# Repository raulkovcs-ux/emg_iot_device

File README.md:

# FAMA-Band: an 8-channel sEMG armband for FAMA-Net

An end-user research device for the **FAMA-Net** thesis (fatigue-aware,
multi-scale adaptive CNN for sEMG gesture recognition). It records
forearm EMG at an exactly known 1 kHz, logs it losslessly, streams it to
the lab PC, and runs FAMA-Net, including both online adaptation tiers,
**on the device**.

| | |
|---|---|
| Channels | 8 bipolar, active dry electrodes (10 mm ENIG, 20 mm IED), driven right leg |
| Sampling | ADS1298 24-bit at 2000 SPS → **1000.00 Hz ± 20 ppm** output, flat ±0.06 dB over 20–450 Hz |
| Noise | 1.61 µVrms input-referred (20–450 Hz, calculated), 105 dB dynamic range |
| Processing | ESP32-S3: thesis pre-processing, STFT [8 × 33 × 9], FAMA-Net, Tier A (causal AdaBN), Tier B (SampEn-triggered head fine-tuning) |
| Data | microSD raw log (2 kSPS) + Wi-Fi UDP or BLE 5 stream, protocol markers in the device timebase |
| Power | 600 mAh Li-Po, ≈5.4 h (BLE) / ≈3.6 h (Wi-Fi) estimated; battery-only while worn with a hardware USB interlock |
| Size | Hub 76 × 50 × 20 mm, pods 19 × 37 × 10.5 mm |
| Prosthesis variant | Electrodes in a transradial socket, **rigid-flex hub** wrapped around the socket, prosthetic-hand interface (UART + 2 proportional outputs) |

## What's in the repository

| Folder | Content | Status |
|---|---|---|
| [`docs/`](docs) | Research, specification, hardware, mechanics, firmware, safety and ethics, bring-up, wearing protocol, thesis mapping | complete |
| [`hardware/`](hardware) | KiCad 7 projects (hub: 4 layers, socket hub: 4-layer rigid-flex, pod: 2 layers), schematic PDFs, Gerbers, BOM and pick-and-place, STEP; Python generators | ERC clean, DRC: 0 errors, 0 unconnected |
| [`mechanical/`](mechanical) | Parametric OpenSCAD: armband enclosures (`famaband.scad`) and transradial socket, electrode cartridges, hub carrier, forearm frame (`socket.scad`); STLs, renders | armband ready to print; socket needs a check-socket fitting |
| [`firmware/`](firmware) | ESP-IDF v5.3 application + portable DSP/ML core (`components/fama_dsp`) | builds (Wi-Fi, BLE and socket/hand-interface variants) |
| [`host/`](host) | Python package `famaband`: reference DSP/model, PyTorch FAMA-Net + exporter, recorder, protocol runner, contact check, simulator; tests | 35 tests passing |

## Documentation

1. [Research: why a custom device, design decisions](docs/01_research.md)
2. [Specification: numbered requirements traced to the thesis](docs/02_specification.md)
3. [Hardware design: circuits, noise, power, safety numbers, PCB](docs/03_hardware_design.md)
4. [Mechanical design](docs/04_mechanical.md)
5. [Firmware and host software](docs/05_firmware.md)
6. [Safety and ethics for use on people](docs/06_safety_and_ethics.md) (**read before any human use**)
7. [Ordering, assembly, bring-up and safety tests](docs/07_assembly_and_bringup.md)
8. [Wearing the band and running a session](docs/08_wearing_and_session_protocol.md)
9. [How the device closes open items of the thesis review sheet](docs/09_thesis_integration.md)
10. [**Prosthetic socket integration and rigid-flex hub**](docs/10_prosthetic_socket.md)

| Socket variant | Rigid-flex socket hub |
|---|---|
|  |  |

| Hub PCB (top) | Pod (top and skin side) |
|---|---|
|  |  |

## Quick start

```bash
make test        # build the C core for the host and run all tests (needs numpy, scipy, pytest; torch optional)
make hardware    # regenerate schematics + PCBs + fab outputs (KiCad 7, Java, xvfb; about 15 min)
make firmware    # ESP-IDF v5.3 build for the ESP32-S3
make stl         # export enclosure STLs (OpenSCAD)

# with a device (or the simulator: python -m famaband.simulator_device)
cd host
python -m famaband.contact                         # electrode contact check
python -m famaband.protocol_runner --subject S01 --day 1
python -m famaband.io recordings/S01_D1_*.fbr --npz s01d1.npz
```

## Verification status, stated honestly

* **Verified in this repository:**
  * the schematics match the source netlist (KiCad's own netlister) and pass ERC
  * both PCBs pass DRC with no unconnected pads
  * the firmware compiles for the ESP32-S3
  * the firmware's signal chain, network runtime, Tier A/B logic and packet format are tested against independent Python references
  * the protocol tools are tested end to end over UDP against a software device
  * the ADS1298 pinout was cross-checked: the stock KiCad 7.0 symbol swaps pins 3/4, and a corrected symbol is used
* **Not yet verified (needs the physical boards):** analog noise and
  CMRR, sample-rate accuracy, battery life, on-device inference timing,
  radio robustness, fault currents and interlock timing. The procedures
  and pass criteria are in [`docs/07_assembly_and_bringup.md`](docs/07_assembly_and_bringup.md).
  Figures marked "estimate" in the docs come from datasheets and
  calculation.
* **Not a medical device.** Research prototype; ethics approval and
  informed consent are required before any recording on people.

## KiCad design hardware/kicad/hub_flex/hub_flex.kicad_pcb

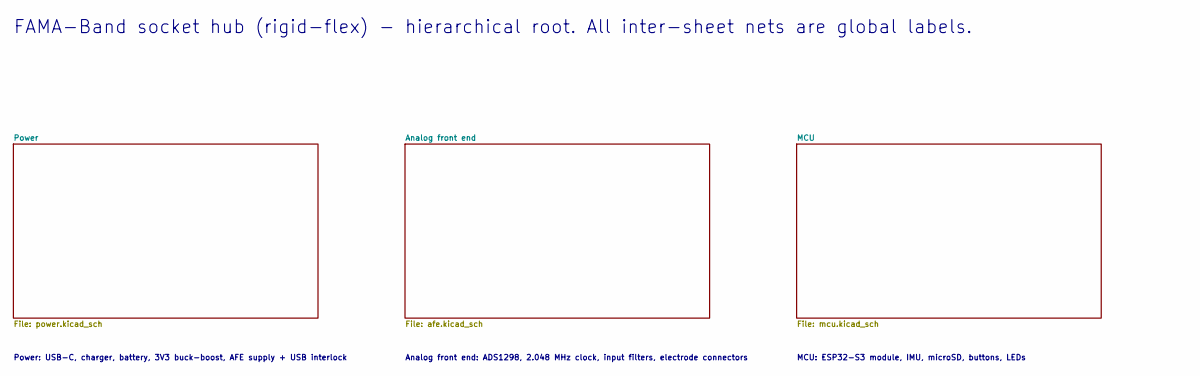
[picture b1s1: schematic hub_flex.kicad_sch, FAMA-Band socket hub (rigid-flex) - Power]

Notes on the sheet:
Power: USB-C, charger, battery, 3V3 buck-boost, AFE supply + USB interlock
Analog front end: ADS1298, 2.048 MHz clock, input filters, electrode connectors
MCU: ESP32-S3 module, IMU, microSD, buttons, LEDs
FAMA-Band socket hub (rigid-flex) - hierarchical root. All inter-sheet nets are global labels.

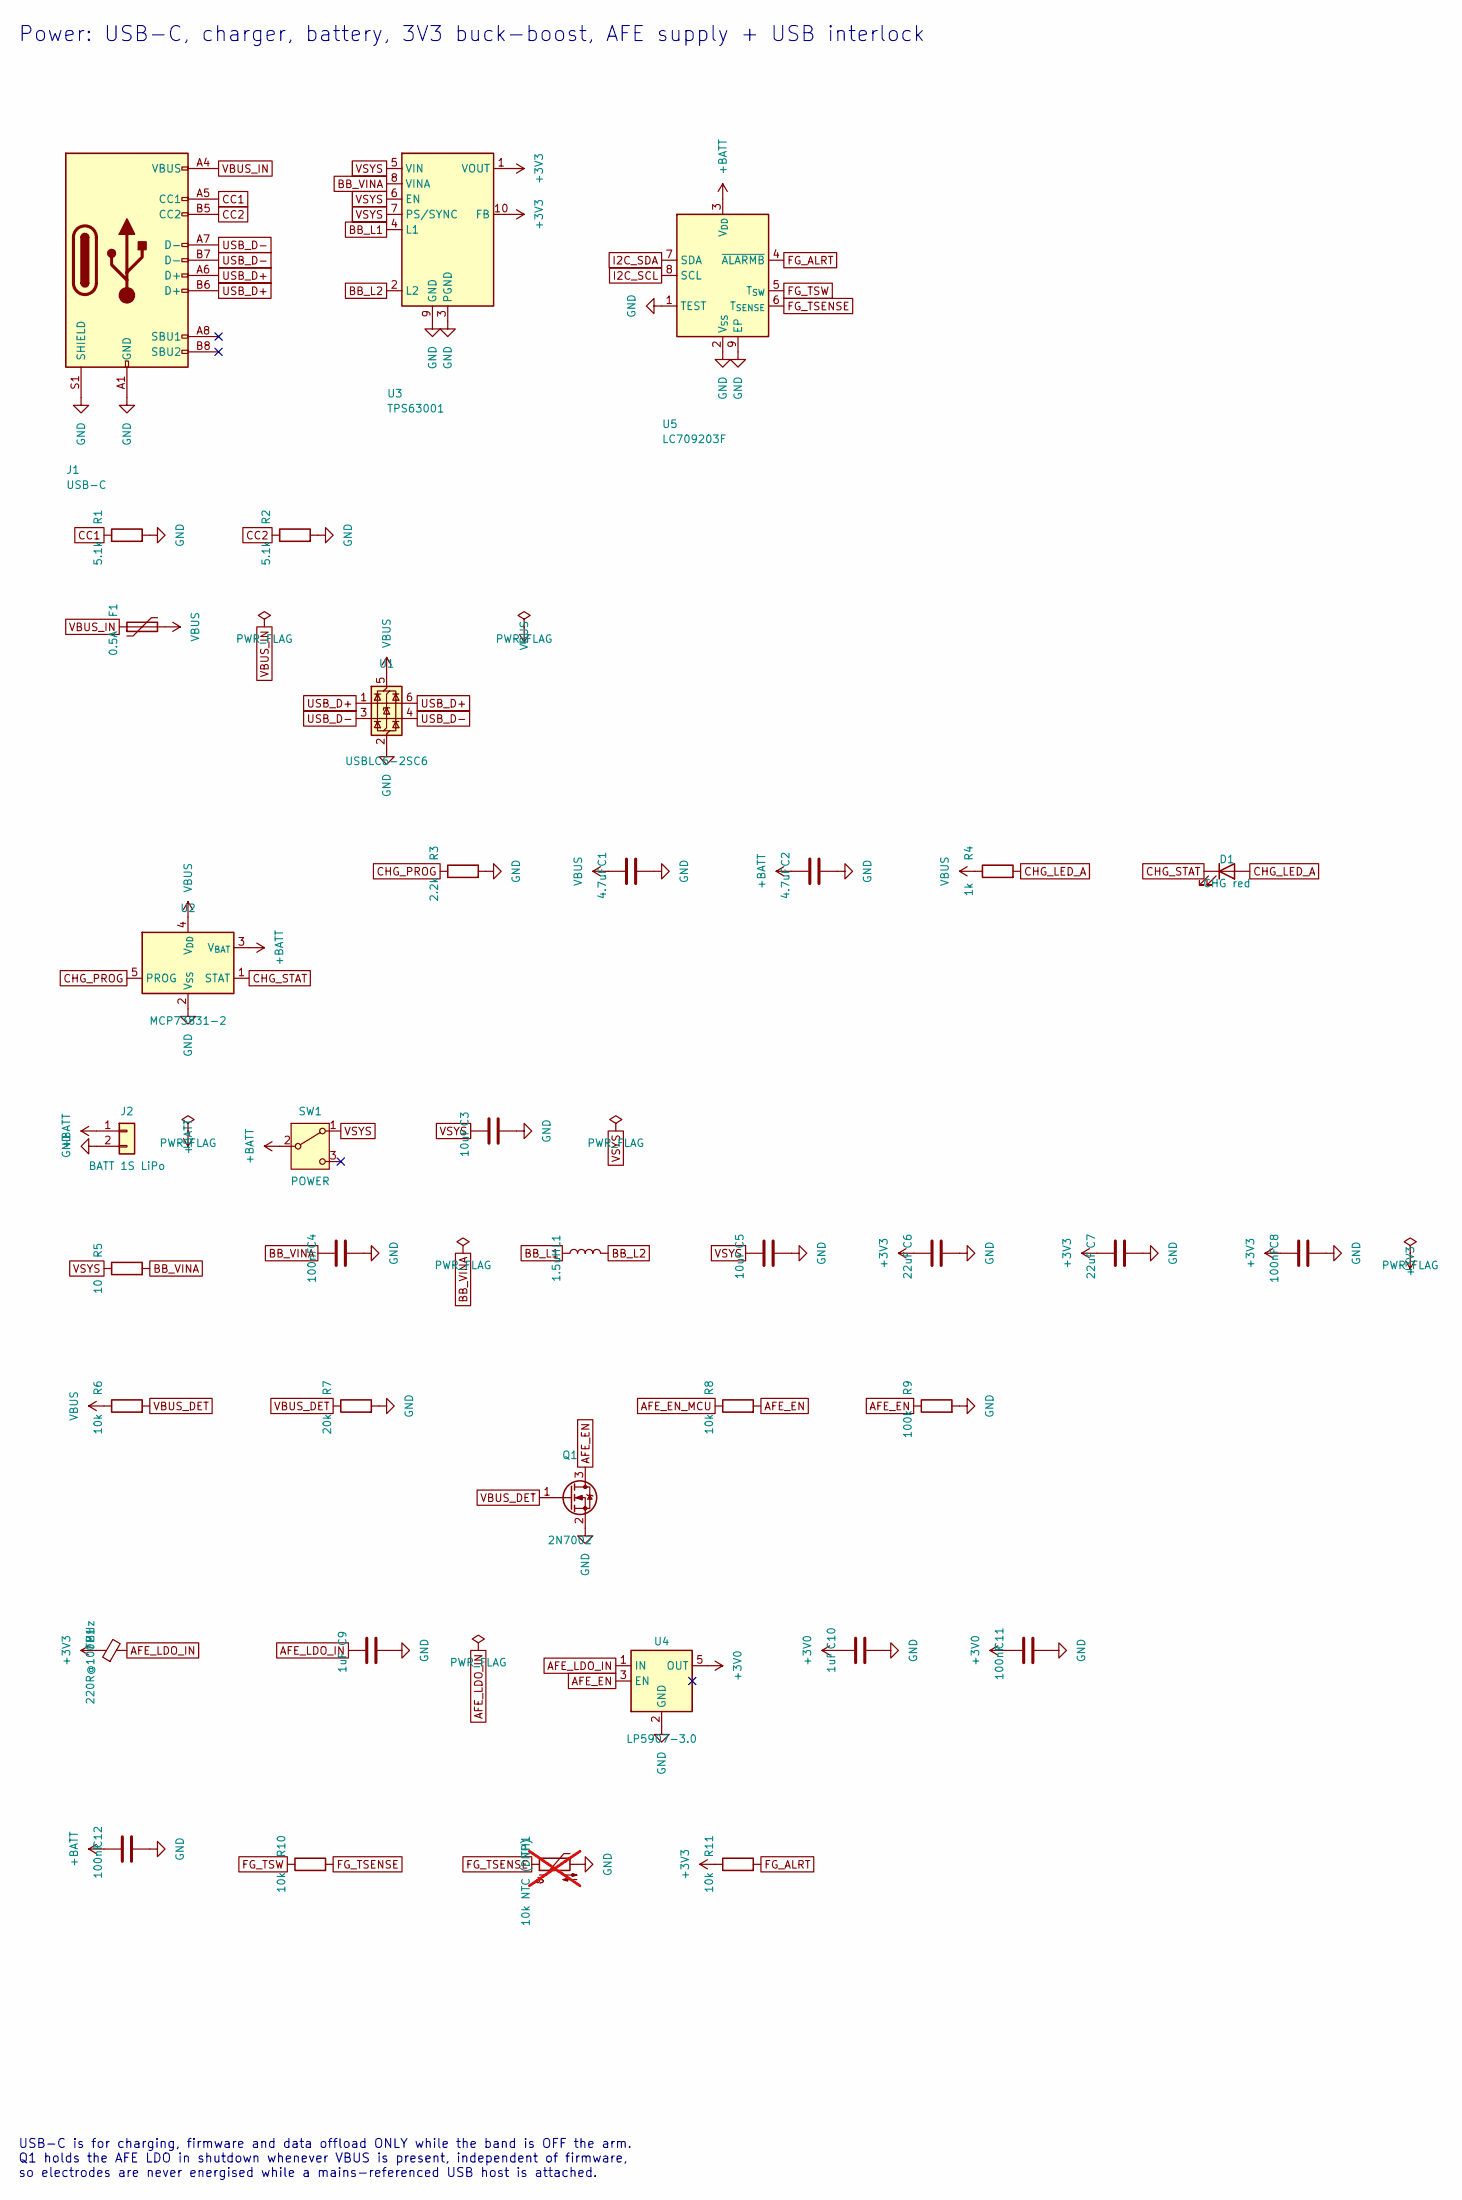
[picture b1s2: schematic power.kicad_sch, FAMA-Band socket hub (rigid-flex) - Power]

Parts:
C1, C2: 4.7uF; C_0603_1608Metric
C3, C5: 10uF; C_0805_2012Metric
C4, C8, C11, C12: 100nF; C_0402_1005Metric
C6, C7: 22uF; C_0805_2012Metric
C9, C10: 1uF; C_0402_1005Metric
D1: CHG red; LED_0603_1608Metric; MPN 150060RS75000
F1: 0.5A; Fuse_0805_2012Metric
FB1: 220R@100MHz; L_0603_1608Metric; MPN BLM18PG221SN1D
J1: USB-C; USB_C_Receptacle_HRO_TYPE-C-31-M-12; MPN TYPE-C-31-M-12
J2: BATT 1S LiPo; JST_PH_S2B-PH-SM4-TB_1x02-1MP_P2.00mm_Horizontal; MPN S2B-PH-SM4-TB(LF)(SN)
L1: 1.5uH; L_Coilcraft_XxL4020; MPN XFL4020-152MEC
Q1: 2N7002; SOT-23; MPN 2N7002
R1, R2: 5.1k; R_0402_1005Metric
R3: 2.2k; R_0402_1005Metric
R4: 1k; R_0402_1005Metric
R5: 10; R_0402_1005Metric
R6, R8, R10, R11: 10k; R_0402_1005Metric
R7: 20k; R_0402_1005Metric
R9: 100k; R_0402_1005Metric
SW1: POWER; SW_SPDT_PCM12; MPN PCM12SMTR
TH1: 10k NTC (DNP); R_0402_1005Metric; MPN NCP15XH103F03RC; not fitted
U1: USBLC6-2SC6; SOT-23-6; MPN USBLC6-2SC6
U2: MCP73831-2; SOT-23-5; MPN MCP73831T-2ACI/OT
U3: TPS63001; Texas_DRC0010J_ThermalVias; MPN TPS63001DRCR
U4: LP5907-3.0; SOT-23-5; MPN LP5907MFX-3.0/NOPB
U5: LC709203F; WDFN-8-1EP_4x3mm_P0.65mm_EP2.4x1.8mm; MPN LC709203FQH-01TWG

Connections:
+3V0: C10.1, C11.1, U4.5 (OUT); also elsewhere on the board
+3V3: C6.1, C7.1, C8.1, FB1.1, R11.1, U3.1 (VOUT), U3.10 (FB); also elsewhere on the board
+BATT: C2.1, C12.1, J2.1, SW1.2 (B), U2.3 (V_{BAT}), U5.3 (V_{DD})
AFE_EN: Q1.3 (D), R8.2, R9.1, U4.3 (EN)
AFE_EN_MCU: R8.1; also elsewhere on the board
AFE_LDO_IN: C9.1, FB1.2, U4.1 (IN)
BB_L1: L1.1, U3.4 (L1)
BB_L2: L1.2, U3.2 (L2)
BB_VINA: C4.1, R5.2, U3.8 (VINA)
CC1: J1.A5 (CC1), R1.1
CC2: J1.B5 (CC2), R2.1
CHG_LED_A: D1.2 (A), R4.2
CHG_PROG: R3.1, U2.5 (PROG)
CHG_STAT: D1.1 (K), U2.1 (STAT)
FG_ALRT: R11.2, U5.4 (~ALARMB); also elsewhere on the board
FG_TSENSE: R10.2, TH1.1, U5.6 (T_{SENSE})
FG_TSW: R10.1, U5.5 (T_{SW})
GND: C1.2, C2.2, C3.2, C4.2, C5.2, C6.2, C7.2, C8.2, C9.2, C10.2, C11.2, C12.2, J1.A1 (GND), J1.A12 (GND), J1.B1 (GND), J1.B12 (GND), J1.S1 (SHIELD), J2.2, Q1.2 (S), R1.2, R2.2, R3.2, R7.2, R9.2, TH1.2, U1.2 (GND), U2.2 (V_{SS}), U3.3 (PGND), U3.9 (GND), U3.11 (PGND), U4.2 (GND), U5.1 (TEST), U5.2 (V_{SS}), U5.9 (EP); also elsewhere on the board
I2C_SCL: U5.8 (SCL); also elsewhere on the board
I2C_SDA: U5.7 (SDA); also elsewhere on the board
USB_D+: J1.A6 (D+), J1.B6 (D+), U1.1 (I/O1), U1.6 (I/O1); also elsewhere on the board
USB_D-: J1.A7 (D-), J1.B7 (D-), U1.3 (I/O2), U1.4 (I/O2); also elsewhere on the board
VBUS: C1.1, F1.2, R4.1, R6.1, U1.5 (VBUS), U2.4 (V_{DD})
VBUS_DET: Q1.1 (G), R6.2, R7.1; also elsewhere on the board
VBUS_IN: F1.1, J1.A4 (VBUS), J1.A9 (VBUS), J1.B4 (VBUS), J1.B9 (VBUS)
VSYS: C3.1, C5.1, R5.1, SW1.1 (A), U3.5 (VIN), U3.6 (EN), U3.7 (PS/SYNC)

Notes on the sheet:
Power: USB-C, charger, battery, 3V3 buck-boost, AFE supply + USB interlock
USB-C is for charging, firmware and data offload ONLY while the band is OFF the arm. Q1 holds the AFE LDO in shutdown whenever VBUS is present, independent of firmware, so electrodes are never energised while a mains-referenced USB host is attached.

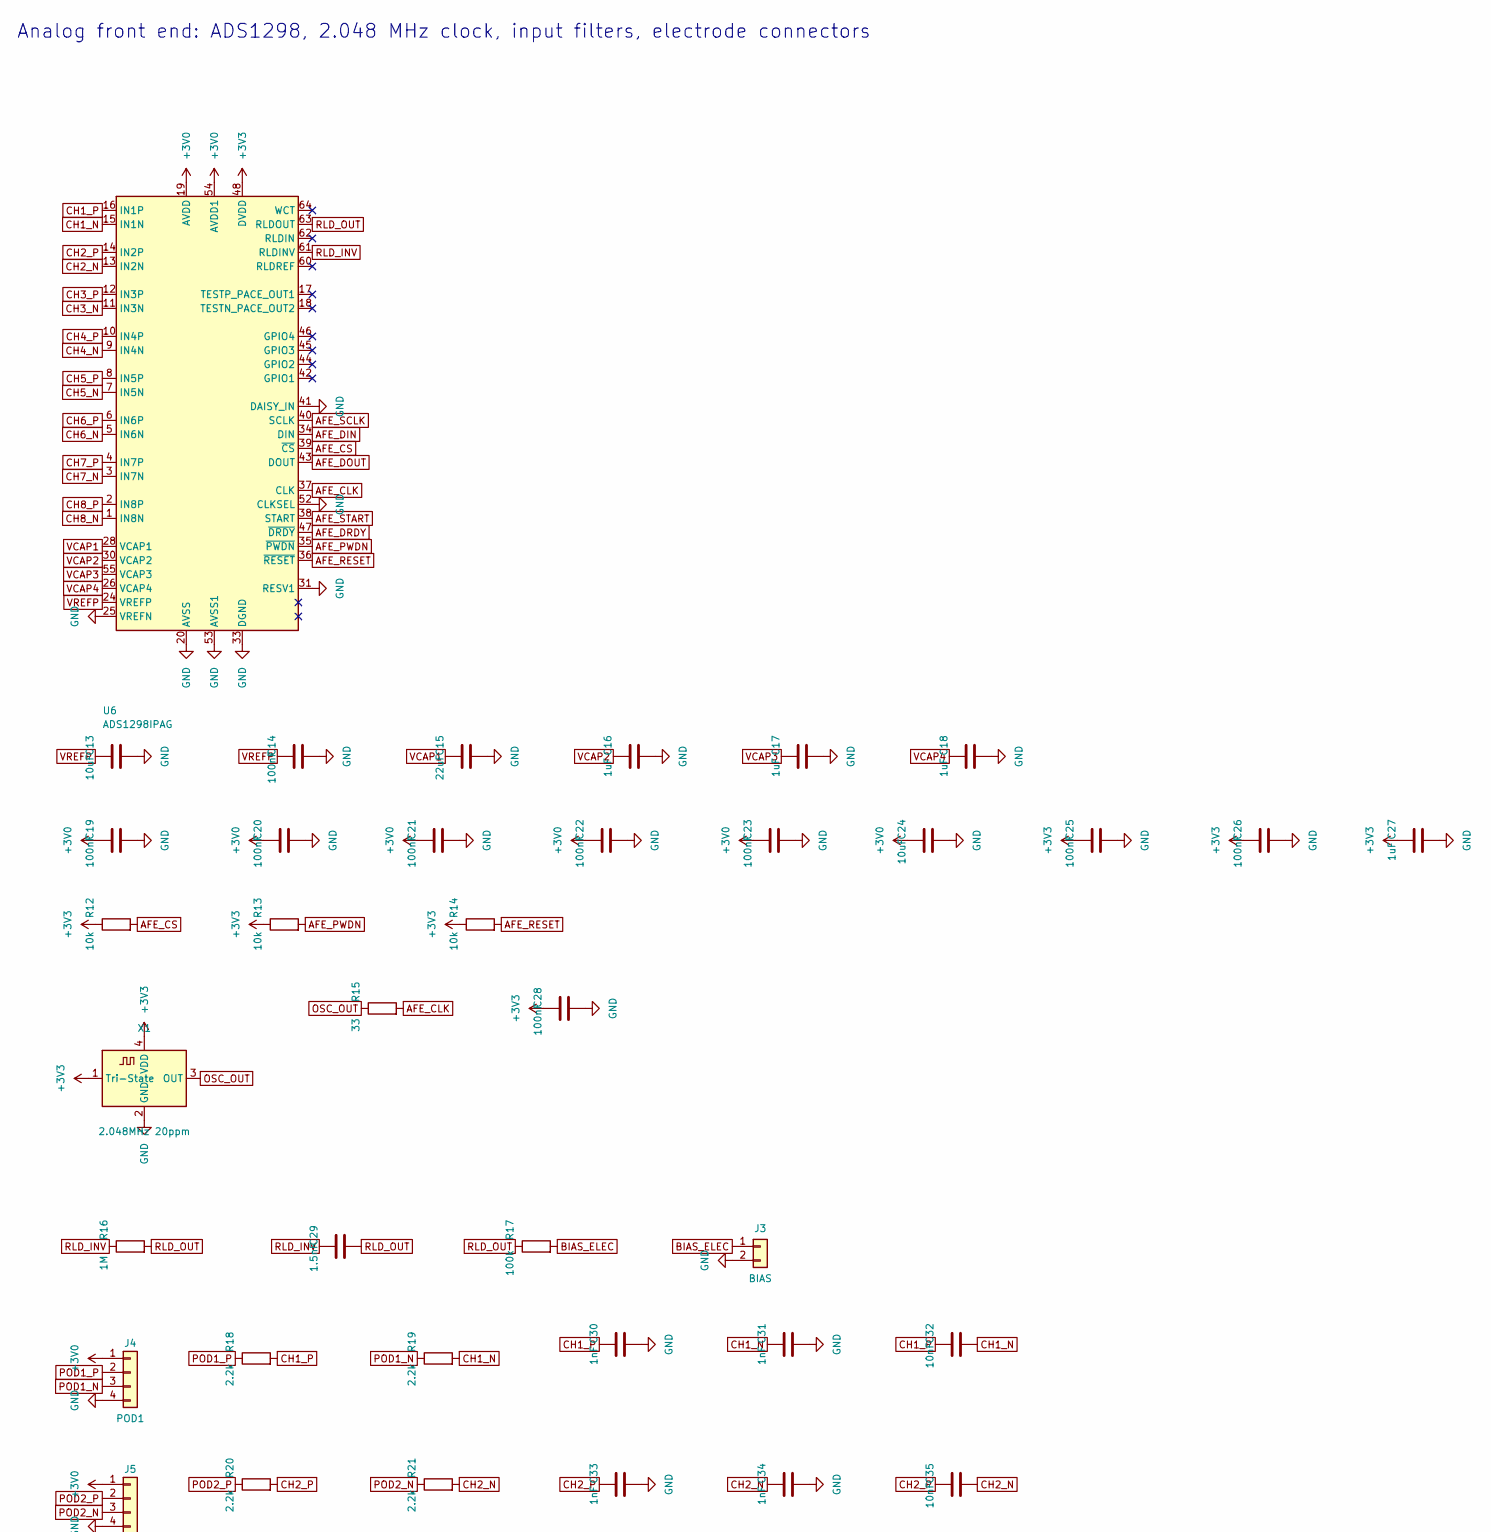
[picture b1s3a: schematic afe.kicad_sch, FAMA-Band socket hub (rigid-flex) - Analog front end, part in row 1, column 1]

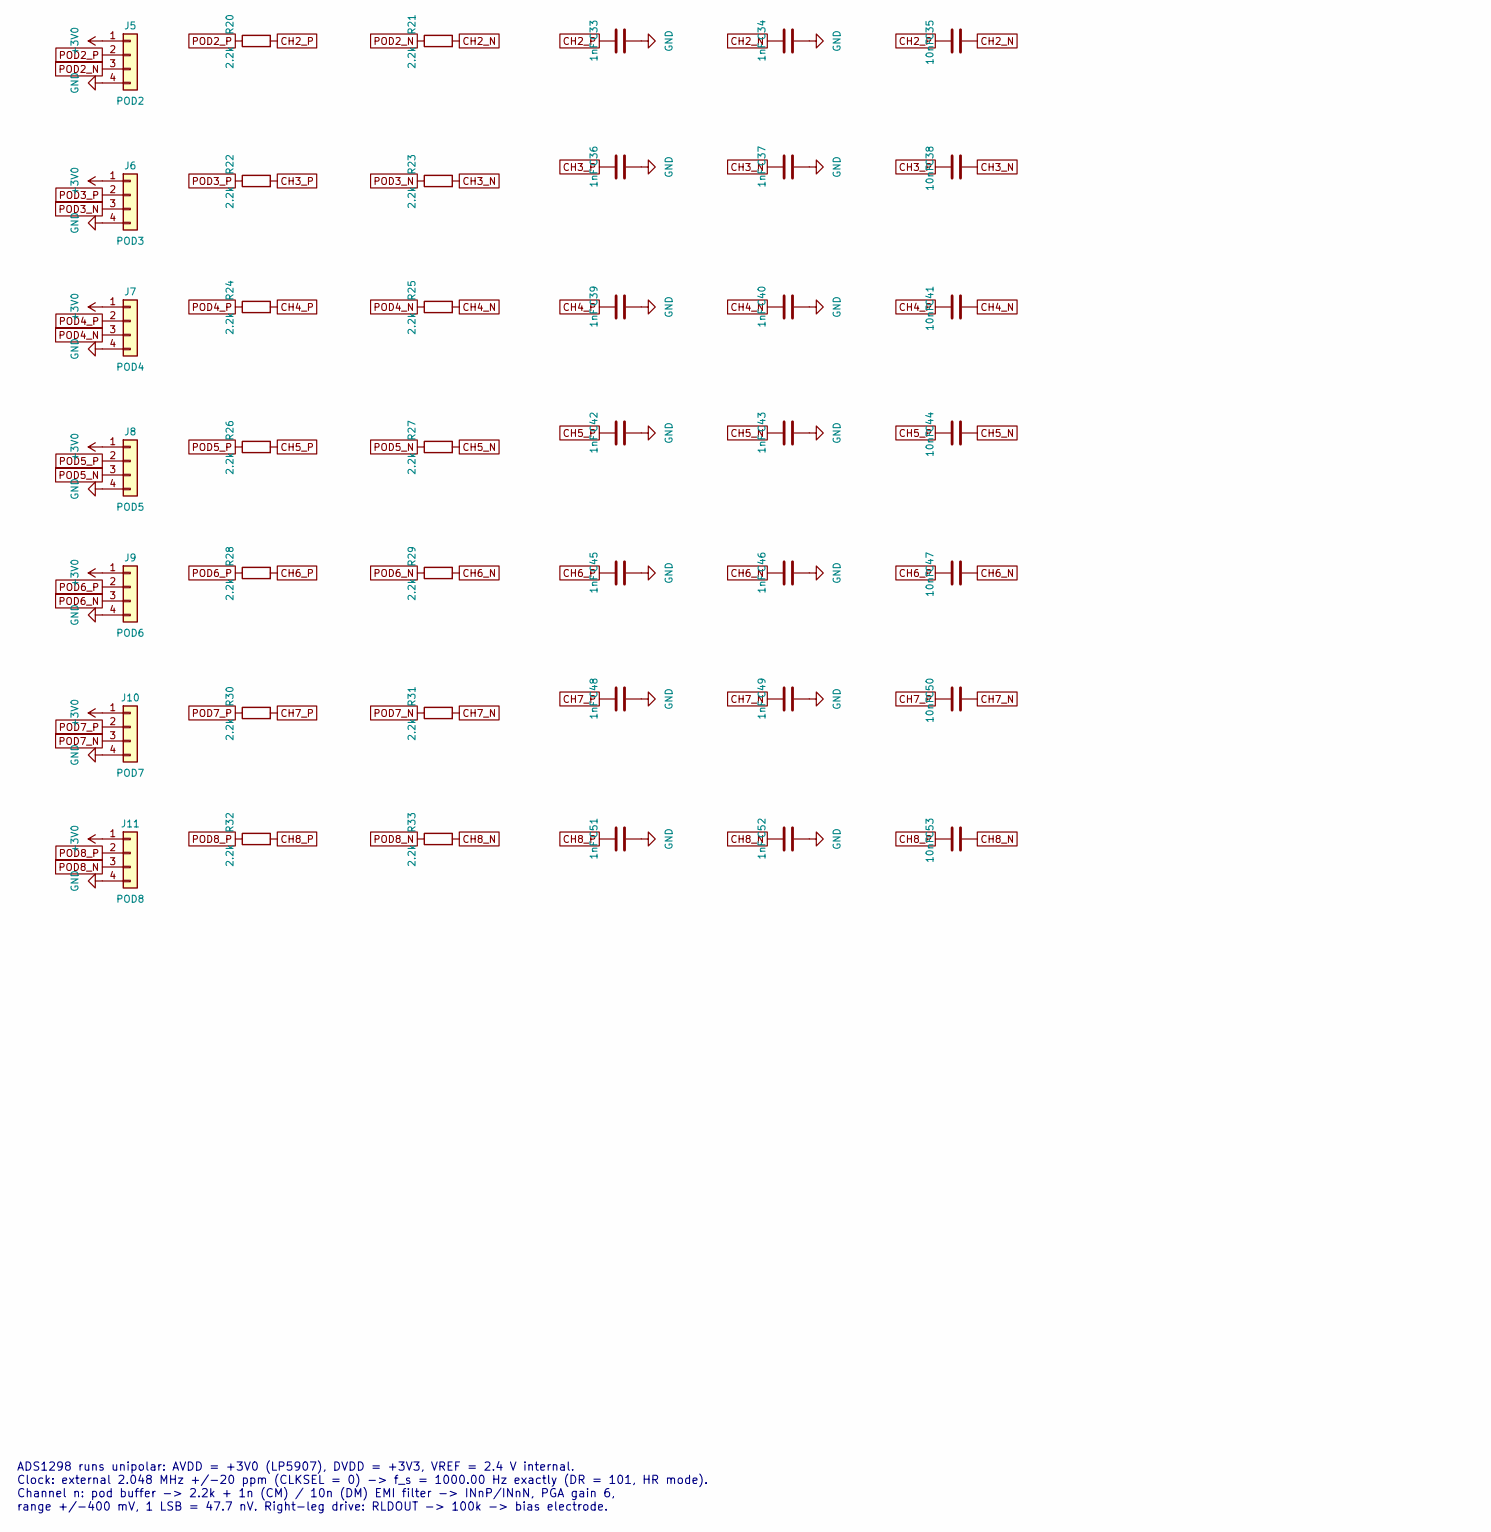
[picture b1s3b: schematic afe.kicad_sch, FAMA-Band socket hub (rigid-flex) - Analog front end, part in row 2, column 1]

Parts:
C13, C24: 10uF; C_0603_1608Metric
C14, C19, C20, C21, C22, C23, C25, C26, C28: 100nF; C_0402_1005Metric
C15: 22uF; C_0805_2012Metric
C16, C17, C18, C27: 1uF; C_0402_1005Metric
C29: 1.5nF; C_0402_1005Metric
C30, C31, C33, C34, C36, C37, C39, C40, C42, C43, C45, C46, C48, C49, C51, C52: 1nF; C_0402_1005Metric
C32, C35, C38, C41, C44, C47, C50, C53: 10nF; C_0402_1005Metric
J3: BIAS; JST_GH_SM02B-GHS-TB_1x02-1MP_P1.25mm_Horizontal; MPN SM02B-GHS-TB(LF)(SN)
J4: POD1; JST_GH_SM04B-GHS-TB_1x04-1MP_P1.25mm_Horizontal; MPN SM04B-GHS-TB(LF)(SN)
J5: POD2; JST_GH_SM04B-GHS-TB_1x04-1MP_P1.25mm_Horizontal; MPN SM04B-GHS-TB(LF)(SN)
J6: POD3; JST_GH_SM04B-GHS-TB_1x04-1MP_P1.25mm_Horizontal; MPN SM04B-GHS-TB(LF)(SN)
J7: POD4; JST_GH_SM04B-GHS-TB_1x04-1MP_P1.25mm_Horizontal; MPN SM04B-GHS-TB(LF)(SN)
J8: POD5; JST_GH_SM04B-GHS-TB_1x04-1MP_P1.25mm_Horizontal; MPN SM04B-GHS-TB(LF)(SN)
J9: POD6; JST_GH_SM04B-GHS-TB_1x04-1MP_P1.25mm_Horizontal; MPN SM04B-GHS-TB(LF)(SN)
J10: POD7; JST_GH_SM04B-GHS-TB_1x04-1MP_P1.25mm_Horizontal; MPN SM04B-GHS-TB(LF)(SN)
J11: POD8; JST_GH_SM04B-GHS-TB_1x04-1MP_P1.25mm_Horizontal; MPN SM04B-GHS-TB(LF)(SN)
R12, R13, R14: 10k; R_0402_1005Metric
R15: 33; R_0402_1005Metric
R16: 1M; R_0402_1005Metric
R17: 100k; R_0603_1608Metric
R18, R19, R20, R21, R22, R23, R24, R25, R26, R27, R28, R29, R30, R31, R32, R33: 2.2k; R_0402_1005Metric
U6: ADS1298IPAG; TQFP-64_10x10mm_P0.5mm; MPN ADS1298IPAG
X1: 2.048MHz 20ppm; Oscillator_SMD_ECS_2520MV-xxx-xx-4Pin_2.5x2.0mm; MPN SiT8008BI-xx-33E-2.048000

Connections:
+3V0: C19.1, C20.1, C21.1, C22.1, C23.1, C24.1, J4.1, J5.1, J6.1, J7.1, J8.1, J9.1, J10.1, J11.1, U6.19 (AVDD), U6.21 (AVDD), U6.22 (AVDD), U6.54 (AVDD1), U6.56 (AVDD), U6.59 (AVDD); also elsewhere on the board
+3V3: C25.1, C26.1, C27.1, C28.1, R12.1, R13.1, R14.1, U6.48 (DVDD), U6.50 (DVDD), X1.1 (Tri-State), X1.4 (VDD); also elsewhere on the board
AFE_CLK: R15.2, U6.37 (CLK)
AFE_CS: R12.2, U6.39 (~CS); also elsewhere on the board
AFE_DIN: U6.34 (DIN); also elsewhere on the board
AFE_DOUT: U6.43 (DOUT); also elsewhere on the board
AFE_DRDY: U6.47 (~DRDY); also elsewhere on the board
AFE_PWDN: R13.2, U6.35 (~PWDN); also elsewhere on the board
AFE_RESET: R14.2, U6.36 (~RESET); also elsewhere on the board
AFE_SCLK: U6.40 (SCLK); also elsewhere on the board
AFE_START: U6.38 (START); also elsewhere on the board
BIAS_ELEC: J3.1, R17.2
CH1_N: C31.1, C32.2, R19.2, U6.15 (IN1N)
CH1_P: C30.1, C32.1, R18.2, U6.16 (IN1P)
CH2_N: C34.1, C35.2, R21.2, U6.13 (IN2N)
CH2_P: C33.1, C35.1, R20.2, U6.14 (IN2P)
CH3_N: C37.1, C38.2, R23.2, U6.11 (IN3N)
CH3_P: C36.1, C38.1, R22.2, U6.12 (IN3P)
CH4_N: C40.1, C41.2, R25.2, U6.9 (IN4N)
CH4_P: C39.1, C41.1, R24.2, U6.10 (IN4P)
CH5_N: C43.1, C44.2, R27.2, U6.7 (IN5N)
CH5_P: C42.1, C44.1, R26.2, U6.8 (IN5P)
CH6_N: C46.1, C47.2, R29.2, U6.5 (IN6N)
CH6_P: C45.1, C47.1, R28.2, U6.6 (IN6P)
CH7_N: C49.1, C50.2, R31.2, U6.3 (IN7N)
CH7_P: C48.1, C50.1, R30.2, U6.4 (IN7P)
CH8_N: C52.1, C53.2, R33.2, U6.1 (IN8N)
CH8_P: C51.1, C53.1, R32.2, U6.2 (IN8P)
GND: C13.2, C14.2, C15.2, C16.2, C17.2, C18.2, C19.2, C20.2, C21.2, C22.2, C23.2, C24.2, C25.2, C26.2, C27.2, C28.2, C30.2, C31.2, C33.2, C34.2, C36.2, C37.2, C39.2, C40.2, C42.2, C43.2, C45.2, C46.2, C48.2, C49.2, C51.2, C52.2, J3.2, J4.4, J5.4, J6.4, J7.4, J8.4, J9.4, J10.4, J11.4, U6.20 (AVSS), U6.23 (AVSS), U6.25 (VREFN), U6.31 (RESV1), U6.32 (AVSS), U6.33 (DGND), U6.41 (DAISY_IN), U6.49 (DGND), U6.51 (DGND), U6.52 (CLKSEL), U6.53 (AVSS1), U6.57 (AVSS), U6.58 (AVSS), X1.2 (GND); also elsewhere on the board
OSC_OUT: R15.1, X1.3 (OUT)
POD1_N: J4.3, R19.1
POD1_P: J4.2, R18.1
POD2_N: J5.3, R21.1
POD2_P: J5.2, R20.1
POD3_N: J6.3, R23.1
POD3_P: J6.2, R22.1
POD4_N: J7.3, R25.1
POD4_P: J7.2, R24.1
POD5_N: J8.3, R27.1
POD5_P: J8.2, R26.1
POD6_N: J9.3, R29.1
POD6_P: J9.2, R28.1
POD7_N: J10.3, R31.1
POD7_P: J10.2, R30.1
POD8_N: J11.3, R33.1
POD8_P: J11.2, R32.1
RLD_INV: C29.1, R16.1, U6.61 (RLDINV)
RLD_OUT: C29.2, R16.2, R17.1, U6.63 (RLDOUT)
VCAP1: C15.1, U6.28 (VCAP1)
VCAP2: C16.1, U6.30 (VCAP2)
VCAP3: C17.1, U6.55 (VCAP3)
VCAP4: C18.1, U6.26 (VCAP4)
VREFP: C13.1, C14.1, U6.24 (VREFP)

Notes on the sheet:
Analog front end: ADS1298, 2.048 MHz clock, input filters, electrode connectors
ADS1298 runs unipolar: AVDD = +3V0 (LP5907), DVDD = +3V3, VREF = 2.4 V internal. Clock: external 2.048 MHz +/-20 ppm (CLKSEL = 0) -> f_s = 1000.00 Hz exactly (DR = 101, HR mode). Channel n: pod buffer -> 2.2k + 1n (CM) / 10n (DM) EMI filter -> INnP/INnN, PGA gain 6, range +/-400 mV, 1 LSB = 47.7 nV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

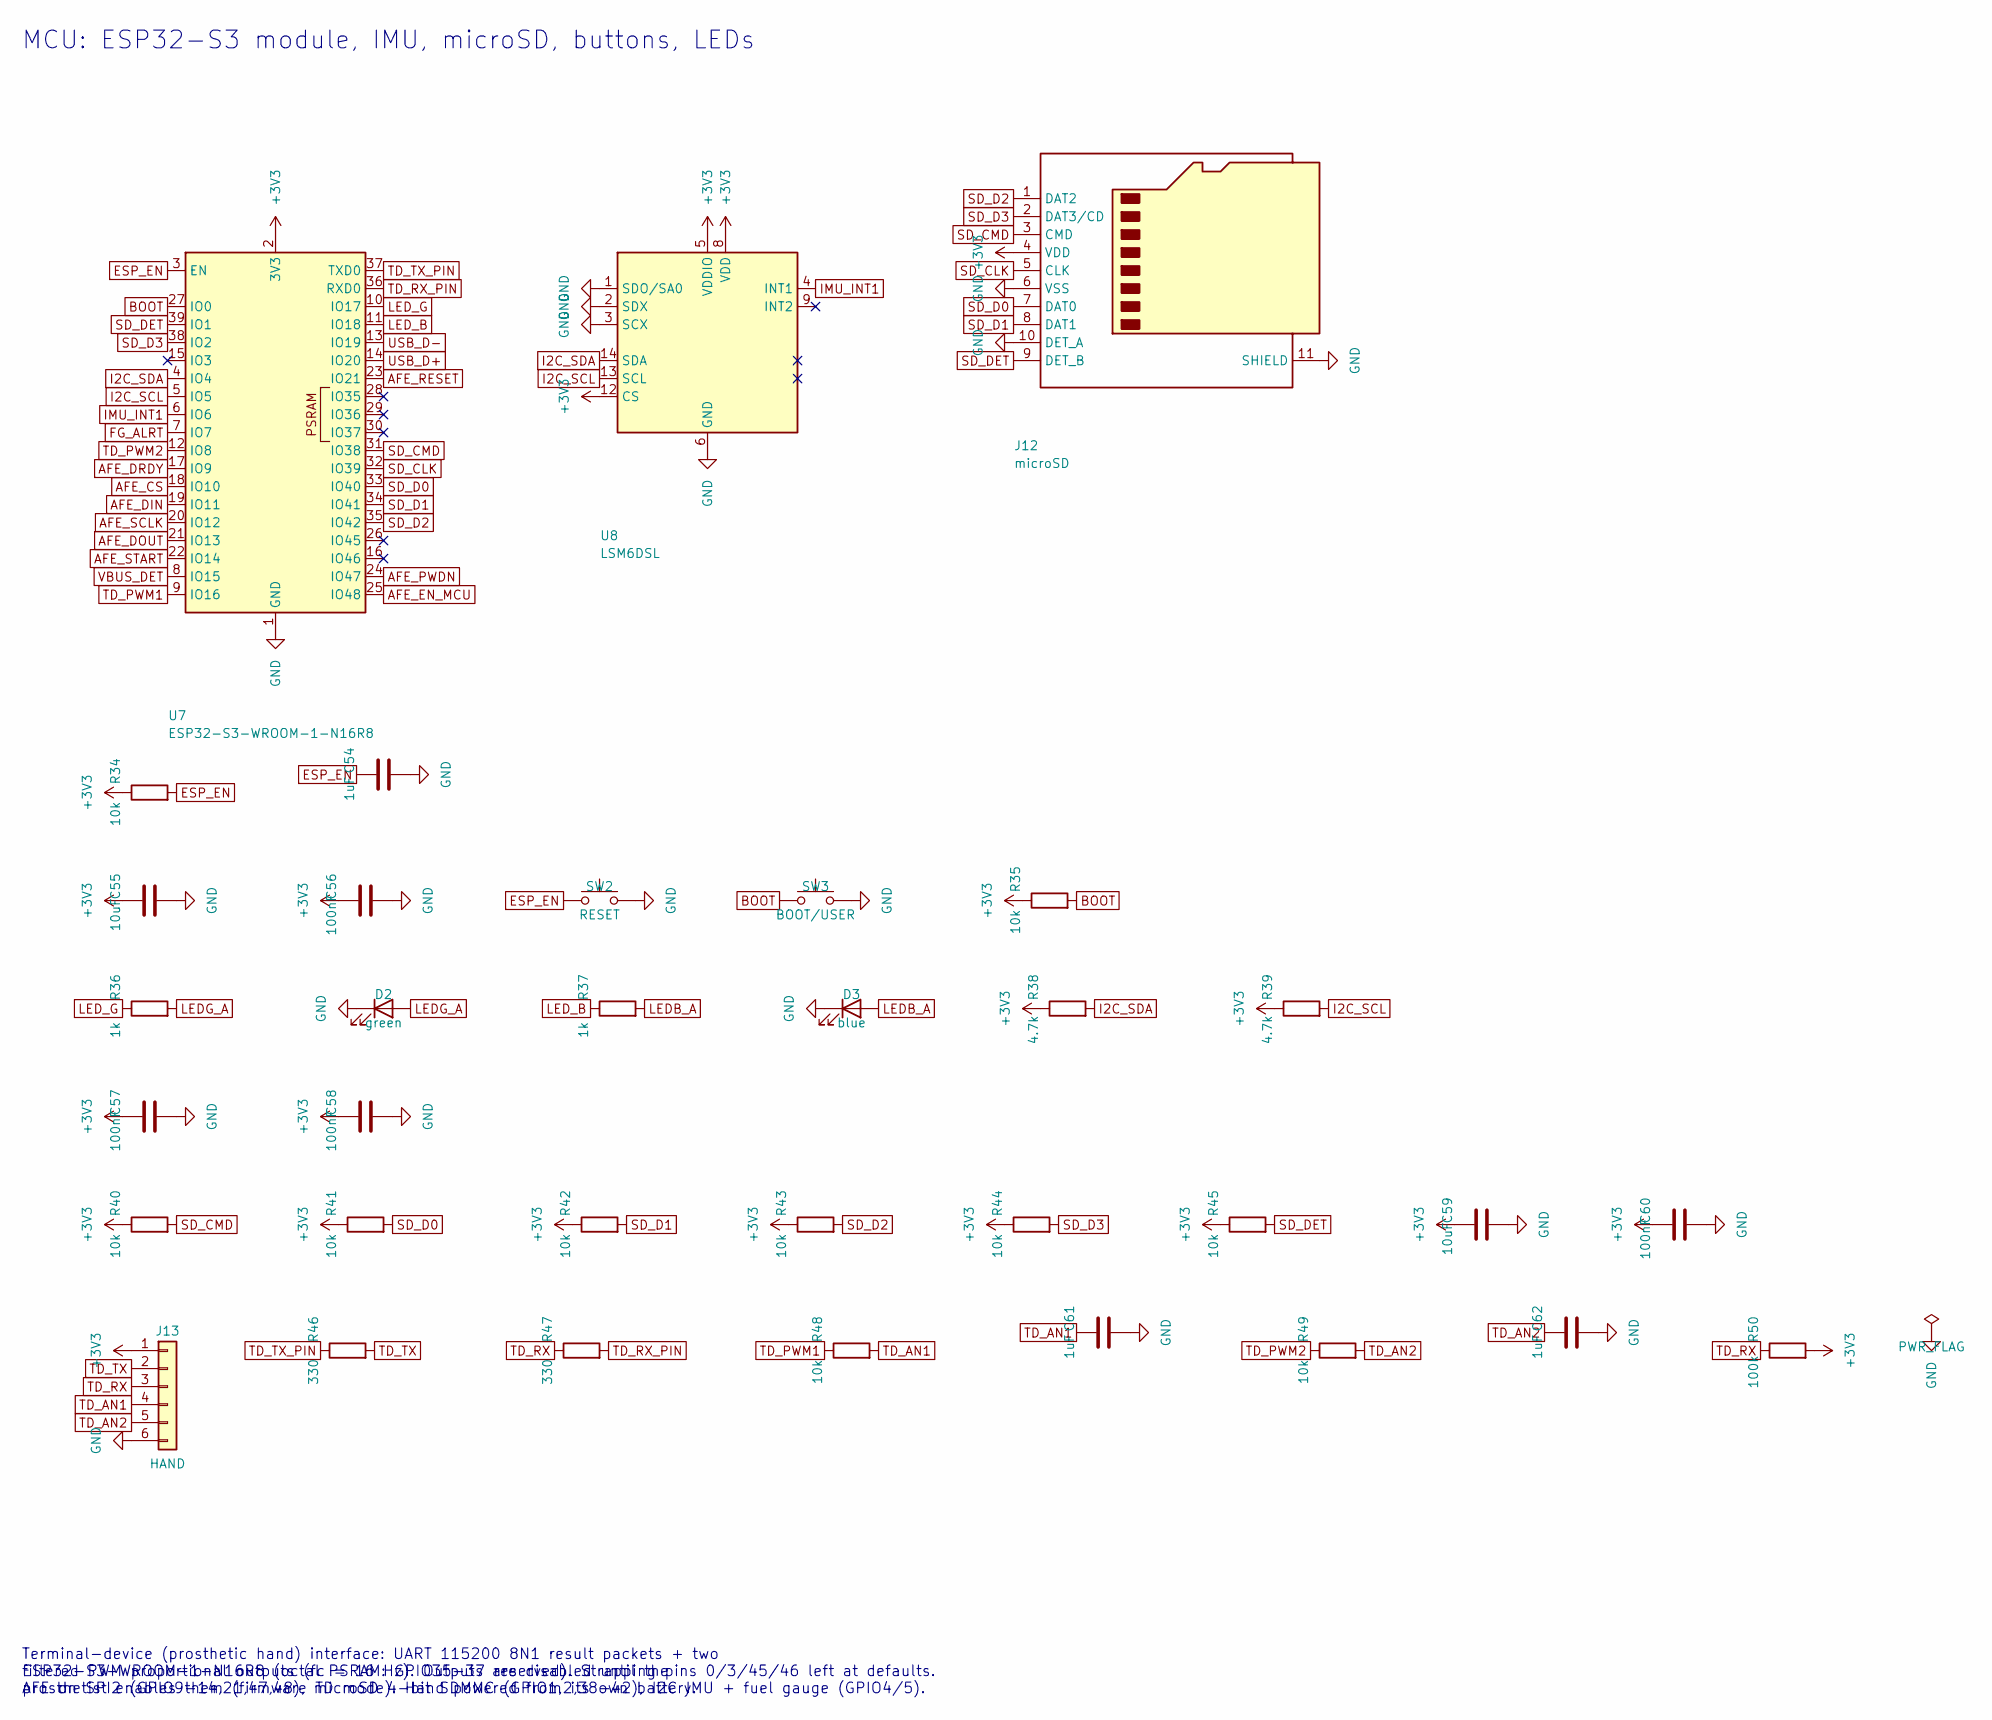
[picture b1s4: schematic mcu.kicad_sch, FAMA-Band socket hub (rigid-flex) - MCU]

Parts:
C54: 1uF; C_0402_1005Metric
C55, C59: 10uF; C_0603_1608Metric
C56, C57, C58, C60: 100nF; C_0402_1005Metric
C61, C62: 1uF; C_0603_1608Metric
D2: green; LED_0603_1608Metric; MPN 150060GS75000
D3: blue; LED_0603_1608Metric; MPN 150060BS75000
J12: microSD; microSD_HC_Hirose_DM3AT-SF-PEJM5; MPN DM3AT-SF-PEJM5
J13: HAND; JST_GH_SM06B-GHS-TB_1x06-1MP_P1.25mm_Horizontal; MPN SM06B-GHS-TB(LF)(SN)
R34, R35, R40, R41, R42, R43, R44, R45, R48, R49: 10k; R_0402_1005Metric
R36, R37: 1k; R_0402_1005Metric
R38, R39: 4.7k; R_0402_1005Metric
R46, R47: 330; R_0402_1005Metric
R50: 100k; R_0402_1005Metric
SW2: RESET; SW_Push_1P1T_NO_CK_KMR2; MPN KMR221GLFS
SW3: BOOT/USER; SW_Push_1P1T_NO_CK_KMR2; MPN KMR221GLFS
U7: ESP32-S3-WROOM-1-N16R8; ESP32-S3-WROOM-1; MPN ESP32-S3-WROOM-1-N16R8
U8: LSM6DSL; LGA-14_3x2.5mm_P0.5mm_LayoutBorder3x4y; MPN LSM6DSLTR

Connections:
+3V3: C55.1, C56.1, C57.1, C58.1, C59.1, C60.1, J12.4 (VDD), J13.1, R34.1, R35.1, R38.1, R39.1, R40.1, R41.1, R42.1, R43.1, R44.1, R45.1, R50.2, U7.2 (3V3), U8.5 (VDDIO), U8.8 (VDD), U8.12 (CS); also elsewhere on the board
AFE_CS: U7.18 (IO10); also elsewhere on the board
AFE_DIN: U7.19 (IO11); also elsewhere on the board
AFE_DOUT: U7.21 (IO13); also elsewhere on the board
AFE_DRDY: U7.17 (IO9); also elsewhere on the board
AFE_EN_MCU: U7.25 (IO48); also elsewhere on the board
AFE_PWDN: U7.24 (IO47); also elsewhere on the board
AFE_RESET: U7.23 (IO21); also elsewhere on the board
AFE_SCLK: U7.20 (IO12); also elsewhere on the board
AFE_START: U7.22 (IO14); also elsewhere on the board
BOOT: R35.2, SW3.1, U7.27 (IO0)
ESP_EN: C54.1, R34.2, SW2.1, U7.3 (EN)
FG_ALRT: U7.7 (IO7); also elsewhere on the board
GND: C54.2, C55.2, C56.2, C57.2, C58.2, C59.2, C60.2, C61.2, C62.2, D2.1 (K), D3.1 (K), J12.6 (VSS), J12.10 (DET_A), J12.11 (SHIELD), J13.6, SW2.2, SW3.2, U7.1 (GND), U7.40 (GND), U7.41 (GND), U8.1 (SDO/SA0), U8.2 (SDX), U8.3 (SCX), U8.6 (GND), U8.7 (GND); also elsewhere on the board
I2C_SCL: R39.2, U7.5 (IO5), U8.13 (SCL); also elsewhere on the board
I2C_SDA: R38.2, U7.4 (IO4), U8.14 (SDA); also elsewhere on the board
IMU_INT1: U7.6 (IO6), U8.4 (INT1)
LEDB_A: D3.2 (A), R37.2
LEDG_A: D2.2 (A), R36.2
LED_B: R37.1, U7.11 (IO18)
LED_G: R36.1, U7.10 (IO17)
SD_CLK: J12.5 (CLK), U7.32 (IO39)
SD_CMD: J12.3 (CMD), R40.2, U7.31 (IO38)
SD_D0: J12.7 (DAT0), R41.2, U7.33 (IO40)
SD_D1: J12.8 (DAT1), R42.2, U7.34 (IO41)
SD_D2: J12.1 (DAT2), R43.2, U7.35 (IO42)
SD_D3: J12.2 (DAT3/CD), R44.2, U7.38 (IO2)
SD_DET: J12.9 (DET_B), R45.2, U7.39 (IO1)
TD_AN1: C61.1, J13.4, R48.2
TD_AN2: C62.1, J13.5, R49.2
TD_PWM1: R48.1, U7.9 (IO16)
TD_PWM2: R49.1, U7.12 (IO8)
TD_RX: J13.3, R47.1, R50.1
TD_RX_PIN: R47.2, U7.36 (RXD0)
TD_TX: J13.2, R46.2
TD_TX_PIN: R46.1, U7.37 (TXD0)
USB_D+: U7.14 (IO20); also elsewhere on the board
USB_D-: U7.13 (IO19); also elsewhere on the board
VBUS_DET: U7.8 (IO15); also elsewhere on the board

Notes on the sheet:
MCU: ESP32-S3 module, IMU, microSD, buttons, LEDs
ESP32-S3-WROOM-1-N16R8 (octal PSRAM: GPIO35-37 reserved). Strapping pins 0/3/45/46 left at defaults. AFE on SPI2 (GPIO9-14,21,47,48), microSD 4-bit SDMMC (GPIO1,2,38-42), I2C IMU + fuel gauge (GPIO4/5).
Terminal-device (prosthetic hand) interface: UART 115200 8N1 result packets + two filtered PWM proportional outputs (fc = 16 Hz). Outputs are disabled until the prosthetist enables them (firmware TD mode). Hand powered from its own battery.

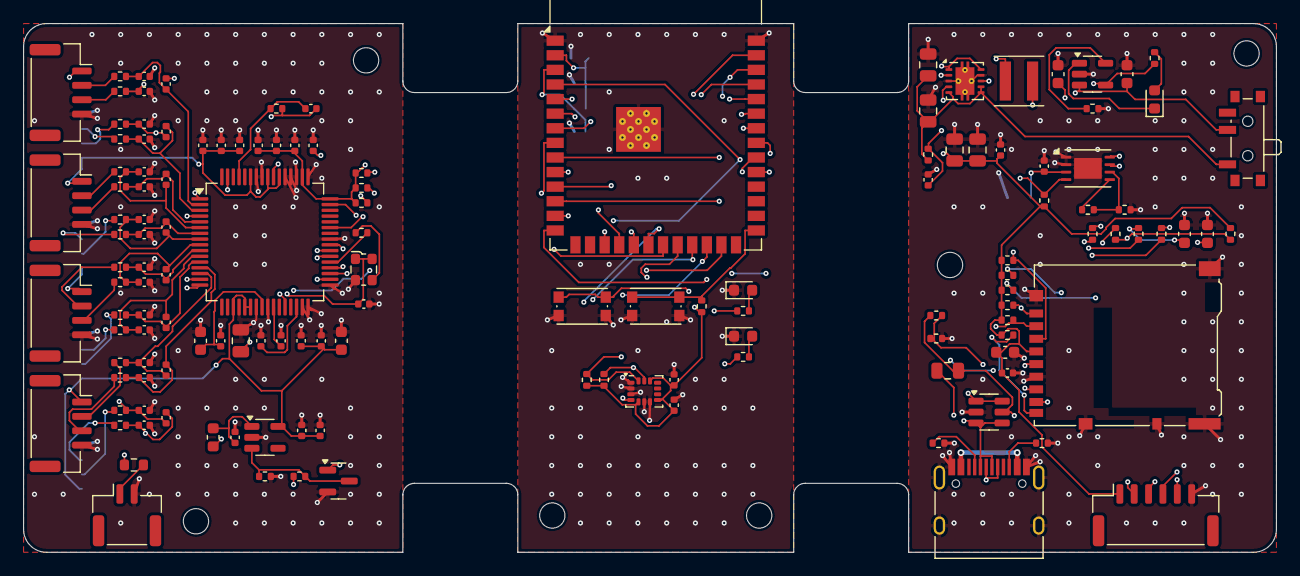
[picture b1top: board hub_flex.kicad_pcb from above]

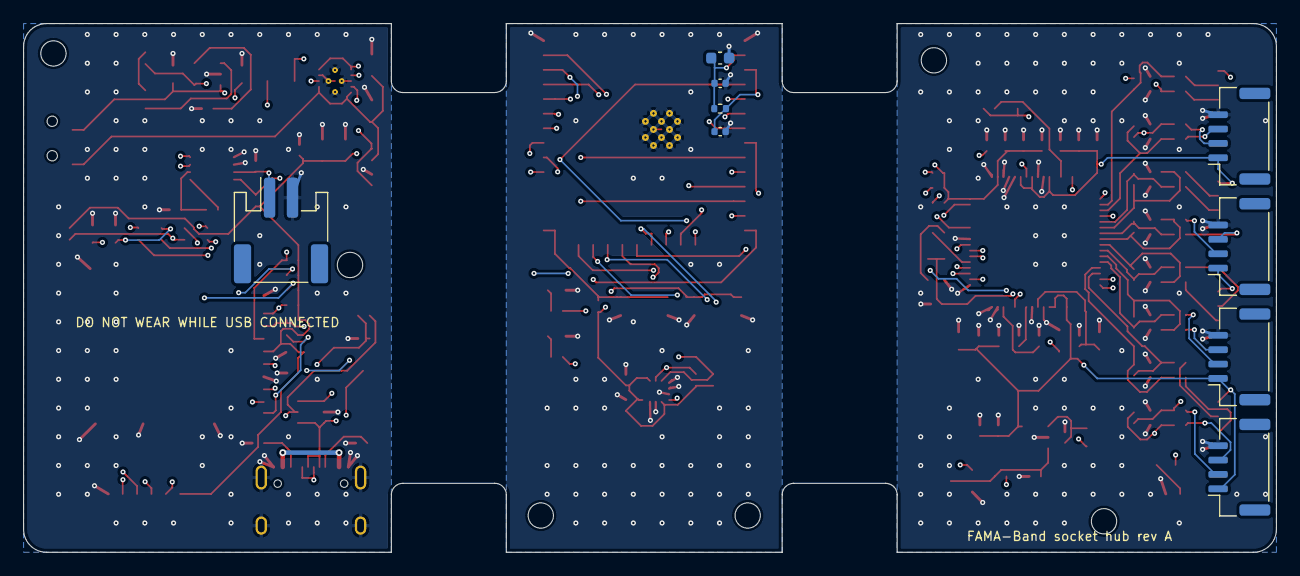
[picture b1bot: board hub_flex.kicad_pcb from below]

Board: 4 copper layers, 109.0 x 46.0 mm, 151 parts (9 on the bottom side), 98 nets.

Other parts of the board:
H1, H2, H3, H4, H5, H6: MountingHole_2.2mm_M2
